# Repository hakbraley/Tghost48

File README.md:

# Tghost48

I made it for learning purposes =V

##Photo

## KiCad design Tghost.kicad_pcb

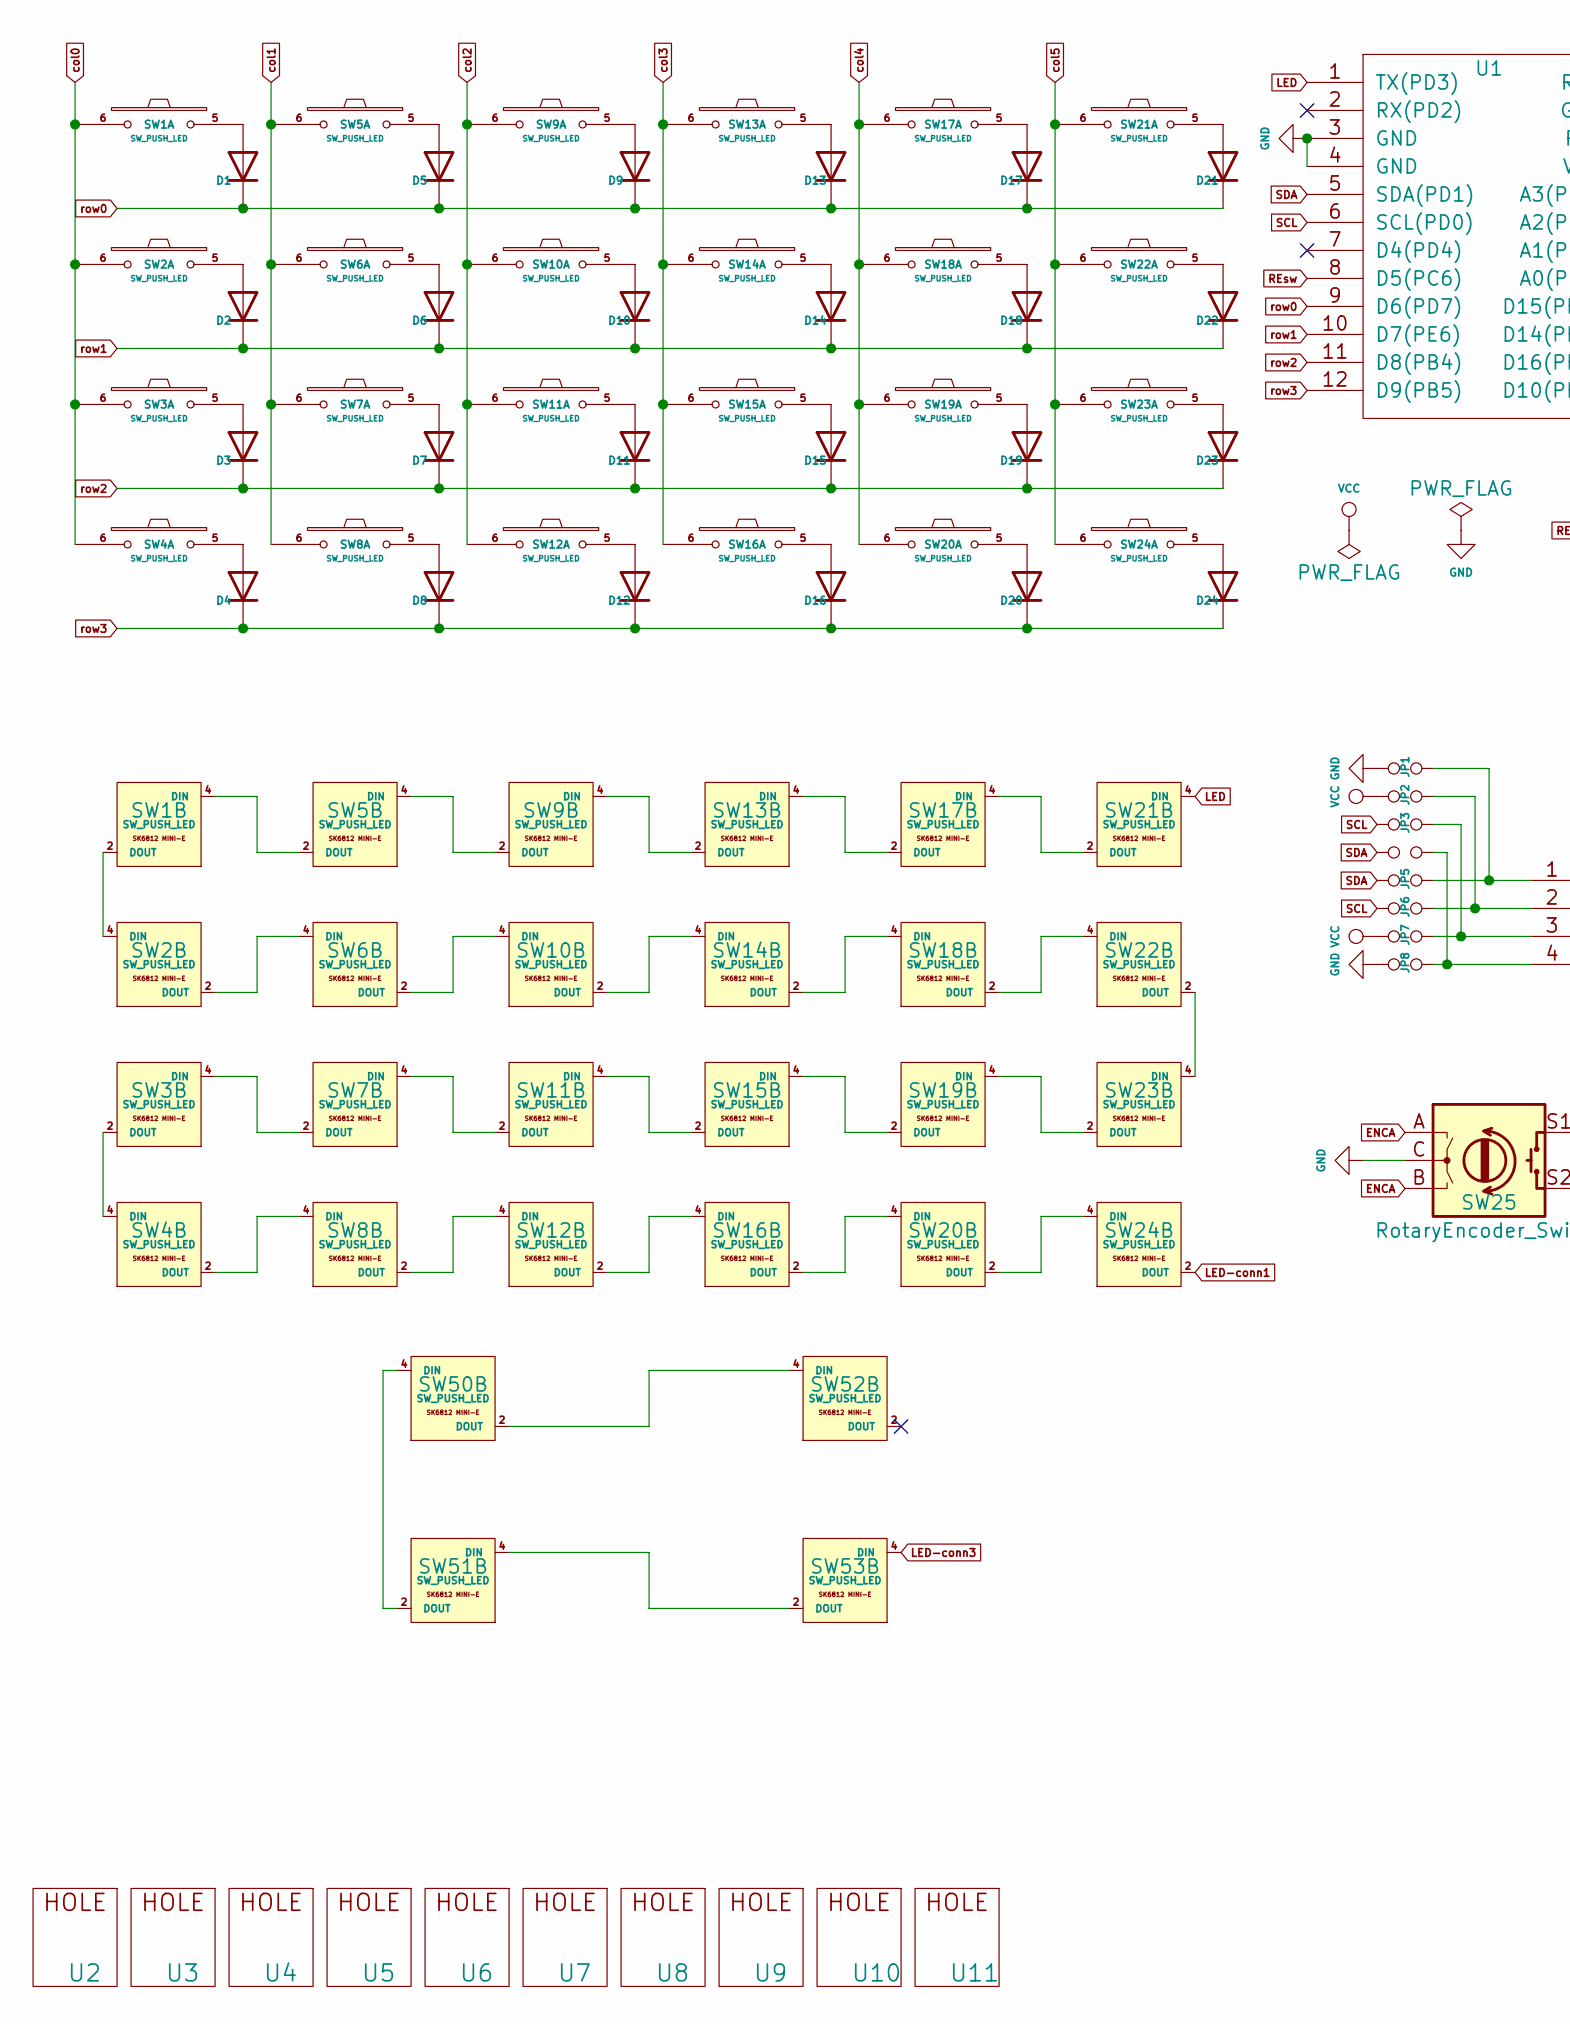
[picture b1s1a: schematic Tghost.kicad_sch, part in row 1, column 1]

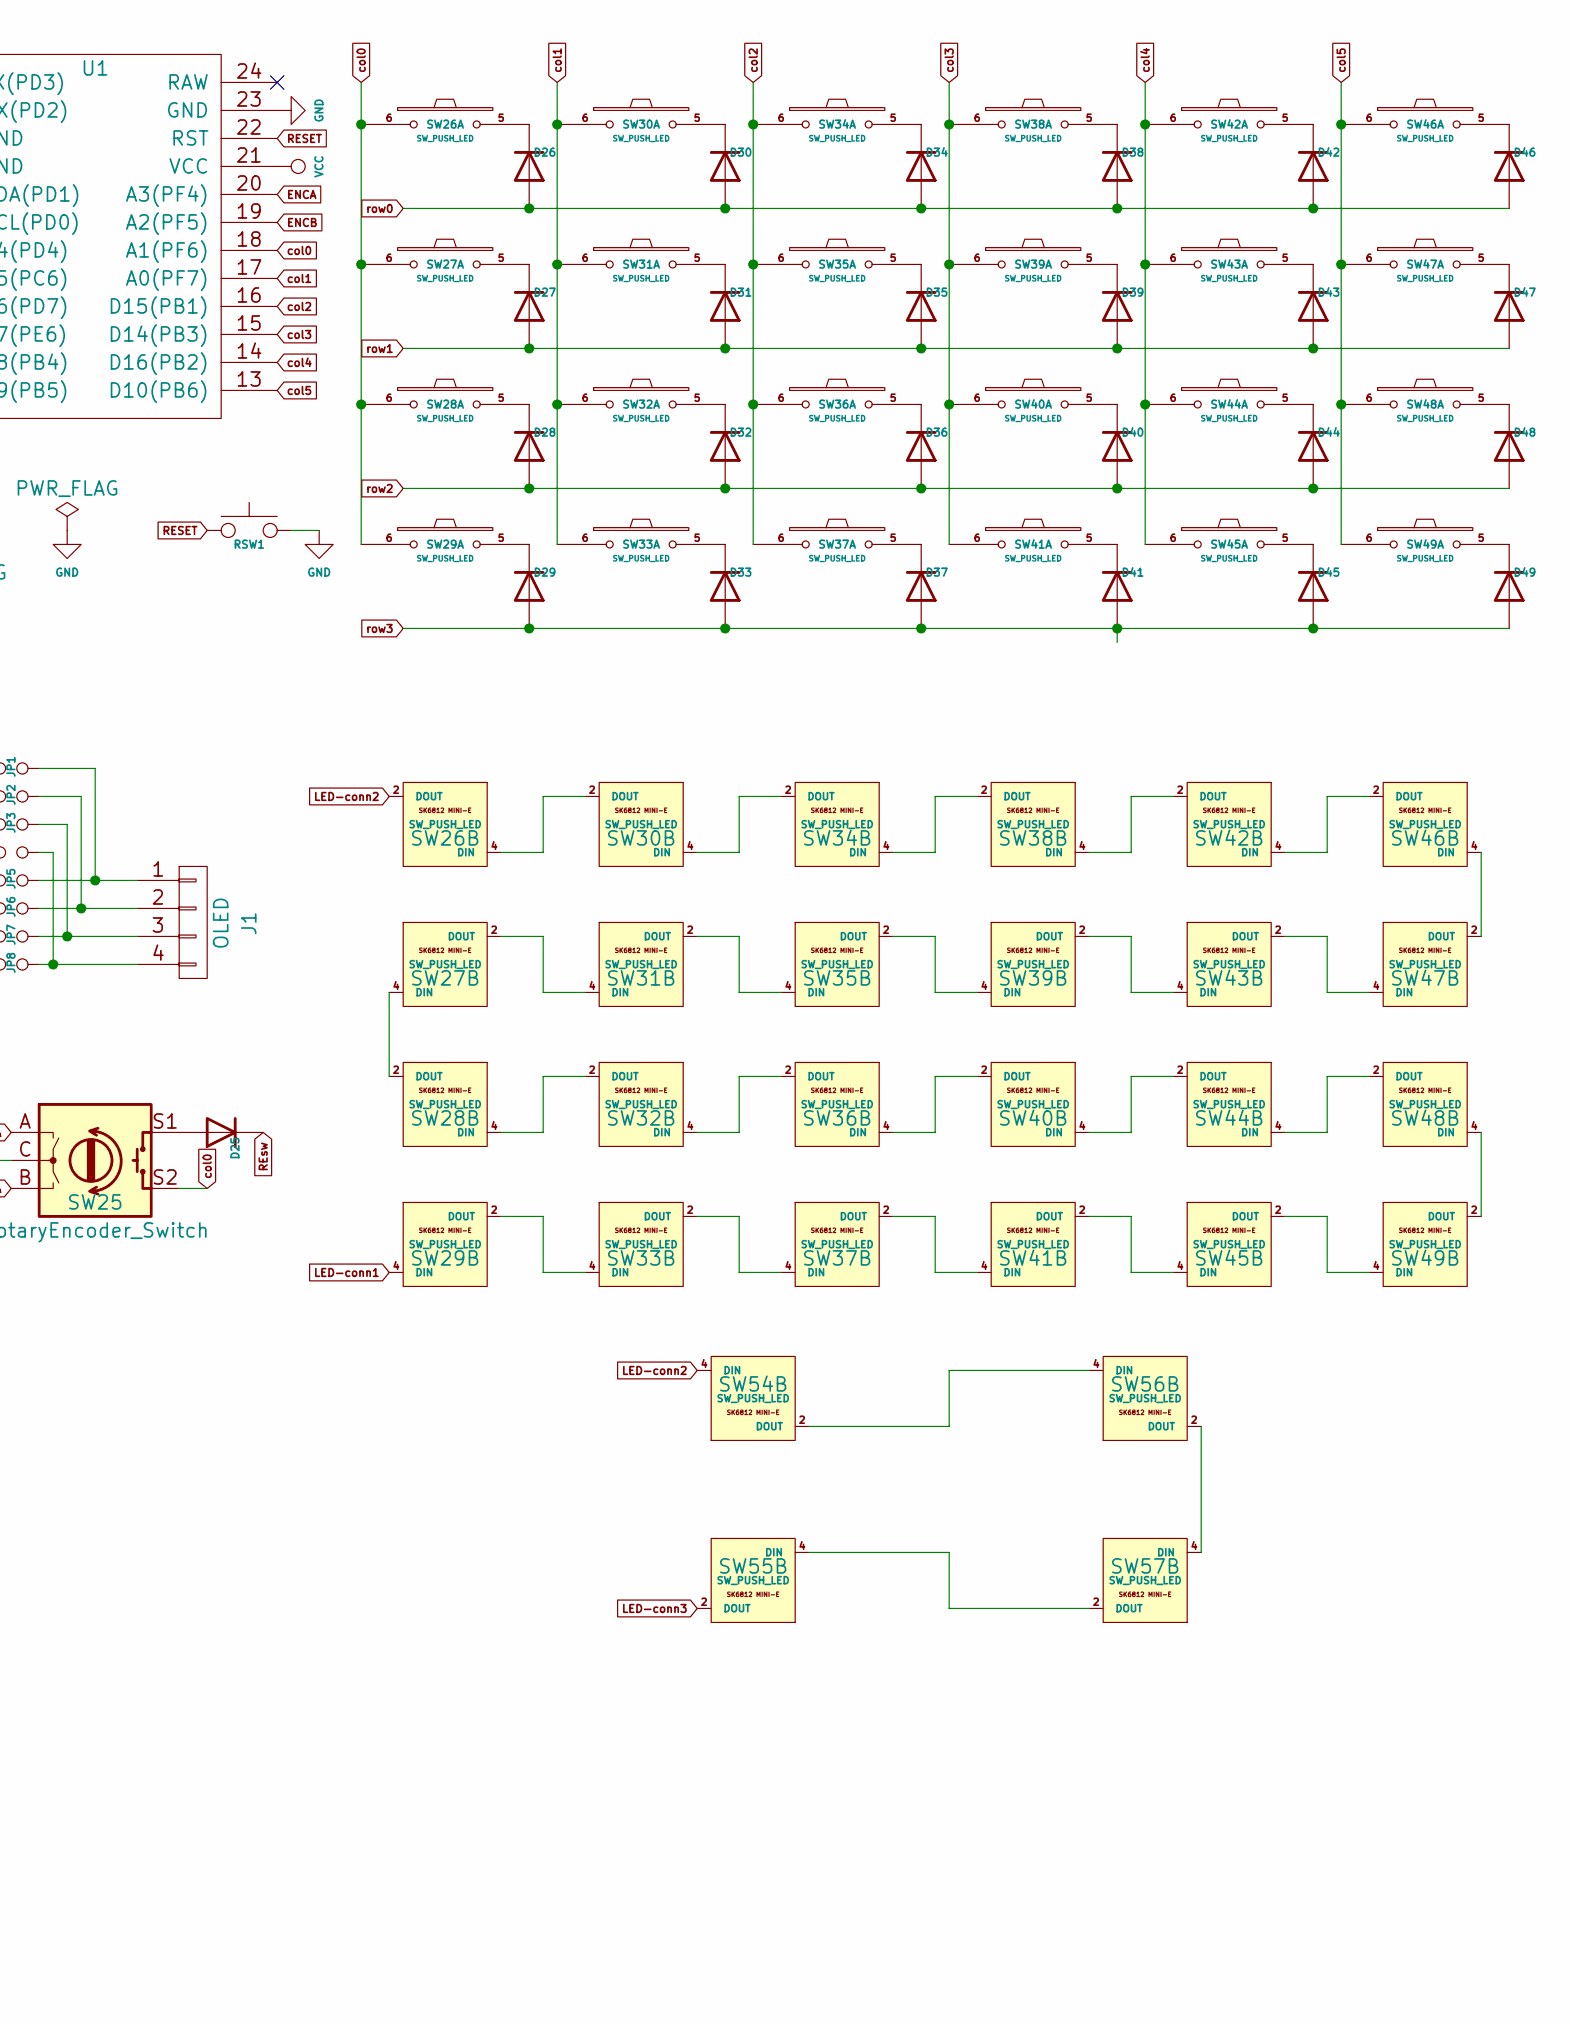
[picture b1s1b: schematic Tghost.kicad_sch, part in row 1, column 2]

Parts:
D1, D2, D3, D4, D5, D6, D7, D8, D9, D10, D11, D12, D13, D14, D15, D16, D17, D18, D19, D20, D21, D22, D23, D24, D25, D26, D27, D28, D29, D30, D31, D32, D33, D34, D35, D36, D37, D38, D39, D40, D41, D42, D43, D44, D45, D46, D47, D48, D49: 1N4148; 1N4841_SMD
J1: OLED; 4pin_oled
JP1, JP2, JP3, JP4, JP5, JP6, JP7, JP8: Jumper
RSW1: SW_RST-Lily58-cache; rst_sw_MX
SW1, SW2, SW3, SW4, SW5, SW6, SW7, SW8, SW9, SW10, SW11, SW12, SW13, SW14, SW15, SW16, SW17, SW18, SW19, SW20, SW21, SW22, SW23, SW24, SW26, SW27, SW28, SW29, SW30, SW31, SW32, SW33, SW34, SW35, SW36, SW37, SW38, SW39, SW40, SW41, SW42, SW43, SW44, SW45, SW46, SW47, SW48, SW49: SW_PUSH_LED; MX-1U-Hotswap&LED
SW25: RotaryEncoder_Switch; REncoder_Alps_EC11E-Switch
SW50, SW51, SW52, SW53, SW54, SW55, SW56, SW57: SW_PUSH_LED; MX_WS2812B
U1: ProMicro; ProMicro_facedown
U2, U3, U4, U5, U6, U7, U8, U9: HOLE-Lily58-cache; lo_oc_to
U10, U11: HOLE-Lily58-cache; lo_oc_nho

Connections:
ENCA: SW25.A, SW25.B, U1.20 (A3(PF4))
ENCB: U1.19 (A2(PF5))
GND: JP1.2, JP8.2, RSW1.2, SW1.3 (GND), SW2.3 (GND), SW3.3 (GND), SW4.3 (GND), SW5.3 (GND), SW6.3 (GND), SW7.3 (GND), SW8.3 (GND), SW9.3 (GND), SW10.3 (GND), SW11.3 (GND), SW12.3 (GND), SW13.3 (GND), SW14.3 (GND), SW15.3 (GND), SW16.3 (GND), SW17.3 (GND), SW18.3 (GND), SW19.3 (GND), SW20.3 (GND), SW21.3 (GND), SW22.3 (GND), SW23.3 (GND), SW24.3 (GND), SW25.C, SW26.3 (GND), SW27.3 (GND), SW28.3 (GND), SW29.3 (GND), SW30.3 (GND), SW31.3 (GND), SW32.3 (GND), SW33.3 (GND), SW34.3 (GND), SW35.3 (GND), SW36.3 (GND), SW37.3 (GND), SW38.3 (GND), SW39.3 (GND), SW40.3 (GND), SW41.3 (GND), SW42.3 (GND), SW43.3 (GND), SW44.3 (GND), SW45.3 (GND), SW46.3 (GND), SW47.3 (GND), SW48.3 (GND), SW49.3 (GND), SW50.3 (GND), SW51.3 (GND), SW52.3 (GND), SW53.3 (GND), SW54.3 (GND), SW55.3 (GND), SW56.3 (GND), SW57.3 (GND), U1.3 (GND), U1.4 (GND), U1.23 (GND)
LED: SW21.4 (DIN), U1.1 (TX(PD3))
LED-conn1: SW24.2 (DOUT), SW29.4 (DIN)
LED-conn2: SW26.2 (DOUT), SW54.4 (DIN)
LED-conn3: SW53.4 (DIN), SW55.2 (DOUT)
unnamed: D1.2 (A), SW1.5
unnamed: D2.2 (A), SW2.5
unnamed: D3.2 (A), SW3.5
unnamed: D4.2 (A), SW4.5
unnamed: D5.2 (A), SW5.5
unnamed: D6.2 (A), SW6.5
unnamed: D7.2 (A), SW7.5
unnamed: D8.2 (A), SW8.5
unnamed: D9.2 (A), SW9.5
unnamed: D10.2 (A), SW10.5
unnamed: D11.2 (A), SW11.5
unnamed: D12.2 (A), SW12.5
unnamed: D13.2 (A), SW13.5
unnamed: D14.2 (A), SW14.5
unnamed: D15.2 (A), SW15.5
unnamed: D16.2 (A), SW16.5
unnamed: D17.2 (A), SW17.5
unnamed: D18.2 (A), SW18.5
unnamed: D19.2 (A), SW19.5
unnamed: D20.2 (A), SW20.5
unnamed: D21.2 (A), SW21.5
unnamed: D22.2 (A), SW22.5
unnamed: D23.2 (A), SW23.5
unnamed: D24.2 (A), SW24.5
unnamed: D25.2 (A), SW25.S1
unnamed: D26.1 (K), SW26.5
unnamed: D27.1 (K), SW27.5
unnamed: D28.1 (K), SW28.5
unnamed: D29.1 (K), SW29.5
unnamed: D30.1 (K), SW30.5
unnamed: D31.1 (K), SW31.5
unnamed: D32.1 (K), SW32.5
unnamed: D33.1 (K), SW33.5
unnamed: D34.1 (K), SW34.5
unnamed: D35.1 (K), SW35.5
unnamed: D36.1 (K), SW36.5
unnamed: D37.1 (K), SW37.5
unnamed: D38.1 (K), SW38.5
unnamed: D39.1 (K), SW39.5
unnamed: D40.1 (K), SW40.5
unnamed: D41.1 (K), SW41.5
unnamed: D42.1 (K), SW42.5
unnamed: D43.1 (K), SW43.5
unnamed: D44.1 (K), SW44.5
unnamed: D45.1 (K), SW45.5
unnamed: D46.1 (K), SW46.5
unnamed: D47.1 (K), SW47.5
unnamed: D48.1 (K), SW48.5
unnamed: D49.1 (K), SW49.5
unnamed: J1.1, JP1.1, JP5.1
unnamed: J1.2, JP2.1, JP6.1
unnamed: J1.3, JP3.1, JP7.1
unnamed: J1.4, JP4.1, JP8.1
unnamed: SW1.2 (DOUT), SW2.4 (DIN)
unnamed: SW1.4 (DIN), SW5.2 (DOUT)
unnamed: SW2.2 (DOUT), SW6.4 (DIN)
unnamed: SW3.2 (DOUT), SW4.4 (DIN)
unnamed: SW3.4 (DIN), SW7.2 (DOUT)
unnamed: SW4.2 (DOUT), SW8.4 (DIN)
unnamed: SW5.4 (DIN), SW9.2 (DOUT)
unnamed: SW10.2 (DOUT), SW14.4 (DIN)
unnamed: SW6.2 (DOUT), SW10.4 (DIN)
unnamed: SW7.4 (DIN), SW11.2 (DOUT)
unnamed: SW11.4 (DIN), SW15.2 (DOUT)
unnamed: SW12.2 (DOUT), SW16.4 (DIN)
unnamed: SW8.2 (DOUT), SW12.4 (DIN)
unnamed: SW9.4 (DIN), SW13.2 (DOUT)
unnamed: SW13.4 (DIN), SW17.2 (DOUT)
unnamed: SW14.2 (DOUT), SW18.4 (DIN)
unnamed: SW15.4 (DIN), SW19.2 (DOUT)
unnamed: SW16.2 (DOUT), SW20.4 (DIN)
unnamed: SW17.4 (DIN), SW21.2 (DOUT)
unnamed: SW18.2 (DOUT), SW22.4 (DIN)
unnamed: SW19.4 (DIN), SW23.2 (DOUT)
unnamed: SW20.2 (DOUT), SW24.4 (DIN)
unnamed: SW22.2 (DOUT), SW23.4 (DIN)
unnamed: SW26.4 (DIN), SW30.2 (DOUT)
unnamed: SW27.2 (DOUT), SW31.4 (DIN)
unnamed: SW27.4 (DIN), SW28.2 (DOUT)
unnamed: SW28.4 (DIN), SW32.2 (DOUT)
unnamed: SW29.2 (DOUT), SW33.4 (DIN)
unnamed: SW30.4 (DIN), SW34.2 (DOUT)
unnamed: SW31.2 (DOUT), SW35.4 (DIN)
unnamed: SW32.4 (DIN), SW36.2 (DOUT)
unnamed: SW33.2 (DOUT), SW37.4 (DIN)
unnamed: SW34.4 (DIN), SW38.2 (DOUT)
unnamed: SW35.2 (DOUT), SW39.4 (DIN)
unnamed: SW36.4 (DIN), SW40.2 (DOUT)
unnamed: SW37.2 (DOUT), SW41.4 (DIN)
unnamed: SW38.4 (DIN), SW42.2 (DOUT)
unnamed: SW39.2 (DOUT), SW43.4 (DIN)
unnamed: SW40.4 (DIN), SW44.2 (DOUT)
unnamed: SW41.2 (DOUT), SW45.4 (DIN)
unnamed: SW42.4 (DIN), SW46.2 (DOUT)
unnamed: SW43.2 (DOUT), SW47.4 (DIN)
unnamed: SW44.4 (DIN), SW48.2 (DOUT)
unnamed: SW45.2 (DOUT), SW49.4 (DIN)
unnamed: SW46.4 (DIN), SW47.2 (DOUT)
unnamed: SW48.4 (DIN), SW49.2 (DOUT)
unnamed: SW50.2 (DOUT), SW52.4 (DIN)
unnamed: SW50.4 (DIN), SW51.2 (DOUT)
unnamed: SW51.4 (DIN), SW53.2 (DOUT)
unnamed: SW54.2 (DOUT), SW56.4 (DIN)
unnamed: SW55.4 (DIN), SW57.2 (DOUT)
unnamed: SW56.2 (DOUT), SW57.4 (DIN)
RESET: RSW1.1, U1.22 (RST)
REsw: D25.1 (K), U1.8 (D5(PC6))
SCL: JP3.2, JP6.2, U1.6 (SCL(PD0))
SDA: JP4.2, JP5.2, U1.5 (SDA(PD1))
VCC: JP2.2, JP7.2, SW1.1 (VCC), SW2.1 (VCC), SW3.1 (VCC), SW4.1 (VCC), SW5.1 (VCC), SW6.1 (VCC), SW7.1 (VCC), SW8.1 (VCC), SW9.1 (VCC), SW10.1 (VCC), SW11.1 (VCC), SW12.1 (VCC), SW13.1 (VCC), SW14.1 (VCC), SW15.1 (VCC), SW16.1 (VCC), SW17.1 (VCC), SW18.1 (VCC), SW19.1 (VCC), SW20.1 (VCC), SW21.1 (VCC), SW22.1 (VCC), SW23.1 (VCC), SW24.1 (VCC), SW26.1 (VCC), SW27.1 (VCC), SW28.1 (VCC), SW29.1 (VCC), SW30.1 (VCC), SW31.1 (VCC), SW32.1 (VCC), SW33.1 (VCC), SW34.1 (VCC), SW35.1 (VCC), SW36.1 (VCC), SW37.1 (VCC), SW38.1 (VCC), SW39.1 (VCC), SW40.1 (VCC), SW41.1 (VCC), SW42.1 (VCC), SW43.1 (VCC), SW44.1 (VCC), SW45.1 (VCC), SW46.1 (VCC), SW47.1 (VCC), SW48.1 (VCC), SW49.1 (VCC), SW50.1 (VCC), SW51.1 (VCC), SW52.1 (VCC), SW53.1 (VCC), SW54.1 (VCC), SW55.1 (VCC), SW56.1 (VCC), SW57.1 (VCC), U1.21 (VCC)
col0: SW1.6, SW2.6, SW3.6, SW4.6, SW25.S2, SW26.6, SW27.6, SW28.6, SW29.6, U1.18 (A1(PF6))
col1: SW5.6, SW6.6, SW7.6, SW8.6, SW30.6, SW31.6, SW32.6, SW33.6, U1.17 (A0(PF7))
col2: SW9.6, SW10.6, SW11.6, SW12.6, SW34.6, SW35.6, SW36.6, SW37.6, U1.16 (D15(PB1))
col3: SW13.6, SW14.6, SW15.6, SW16.6, SW38.6, SW39.6, SW40.6, SW41.6, U1.15 (D14(PB3))
col4: SW17.6, SW18.6, SW19.6, SW20.6, SW42.6, SW43.6, SW44.6, SW45.6, U1.14 (D16(PB2))
col5: SW21.6, SW22.6, SW23.6, SW24.6, SW46.6, SW47.6, SW48.6, SW49.6, U1.13 (D10(PB6))
row0: D1.1 (K), D5.1 (K), D9.1 (K), D13.1 (K), D17.1 (K), D21.1 (K), D26.2 (A), D30.2 (A), D34.2 (A), D38.2 (A), D42.2 (A), D46.2 (A), U1.9 (D6(PD7))
row1: D2.1 (K), D6.1 (K), D10.1 (K), D14.1 (K), D18.1 (K), D22.1 (K), D27.2 (A), D31.2 (A), D35.2 (A), D39.2 (A), D43.2 (A), D47.2 (A), U1.10 (D7(PE6))
row2: D3.1 (K), D7.1 (K), D11.1 (K), D15.1 (K), D19.1 (K), D23.1 (K), D28.2 (A), D32.2 (A), D36.2 (A), D40.2 (A), D44.2 (A), D48.2 (A), U1.11 (D8(PB4))
row3: D4.1 (K), D8.1 (K), D12.1 (K), D16.1 (K), D20.1 (K), D24.1 (K), D29.2 (A), D33.2 (A), D37.2 (A), D41.2 (A), D45.2 (A), D49.2 (A), U1.12 (D9(PB5))

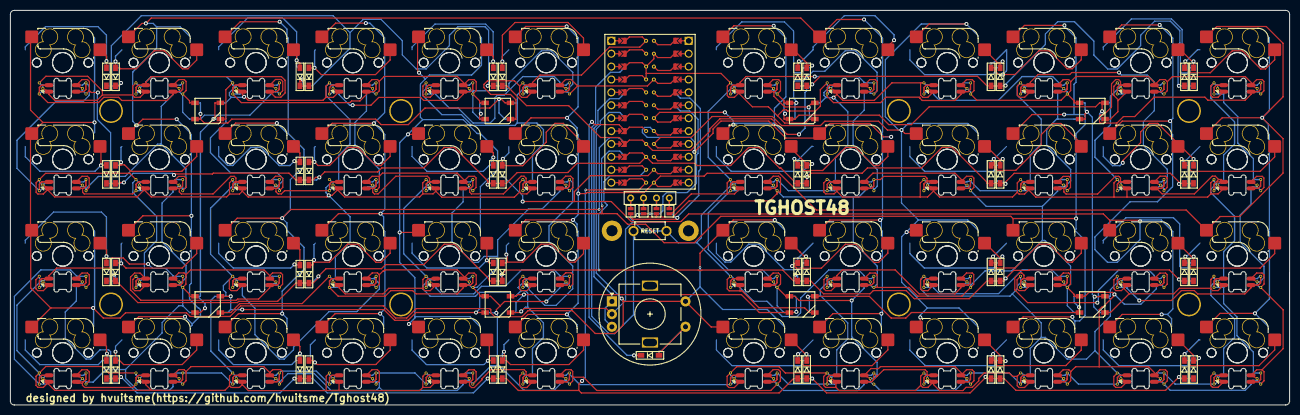
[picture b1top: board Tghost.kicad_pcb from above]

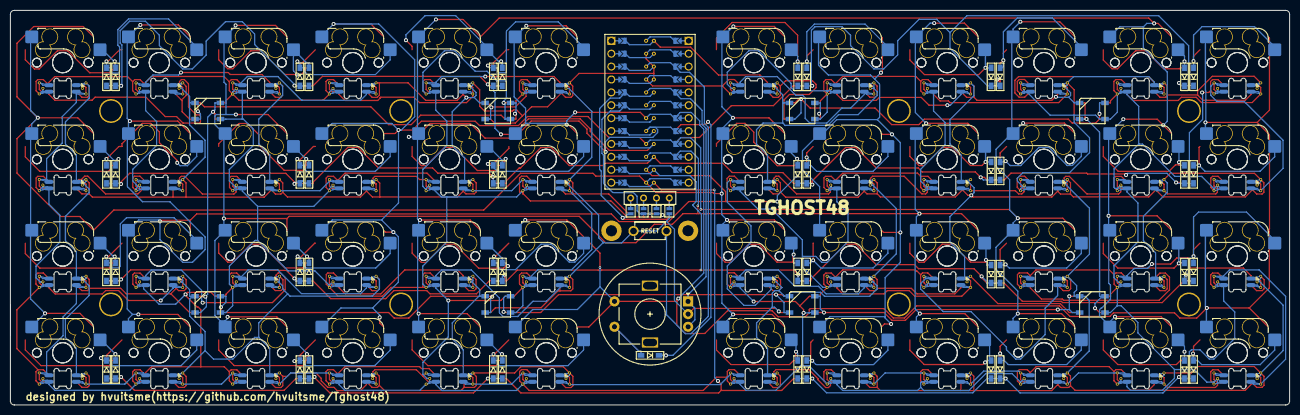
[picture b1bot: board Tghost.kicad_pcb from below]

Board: 2 copper layers, 252.0 x 77.7 mm, 127 parts (4 on the bottom side), 126 nets.

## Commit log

2023-04-11 extra unneeded row in layout macro
2023-04-11 fixed column pin definitions
2023-04-11 fixed layout macro
2023-04-11 fixed matrix size
2023-04-11 fixed matrix and encoder defs
2023-04-11 deleted unnecessary options
2023-04-11 add rgb definitions and led map
2023-04-11 moved usb info to info.json
2023-04-11 rgblight_enable ifdef guard
2023-04-11 fixed layout macro matrix
2023-04-11 removed extra comma
2023-04-11 fixed matrix.c
2023-04-11 fixed matrix pin definitions
2023-04-11 fixed underscore instead of hyphen
2023-04-11 fixed keymap errors
2023-04-11 SUCCESSFUL COMPILE, READY FOR TESTING
2023-04-18 Fixed matrix scanning
    Tested keys on both sides with breadboard.
2023-04-18 SUCCESSFUL COMPILE
